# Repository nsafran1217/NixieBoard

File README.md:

This repo contains an Arduino Library and board disign files for a 6 digit IN-12 Nixie tube board with INS-1 colons.

The board uses K155ID1 drivers to control the tubes.

This is a smaller version of my original Nixie tube clock board: https://github.com/nsafran1217/arduino-nixie-clock

Used in my Nixie Weather Clock project: https://github.com/nsafran1217/NixieWeatherClock

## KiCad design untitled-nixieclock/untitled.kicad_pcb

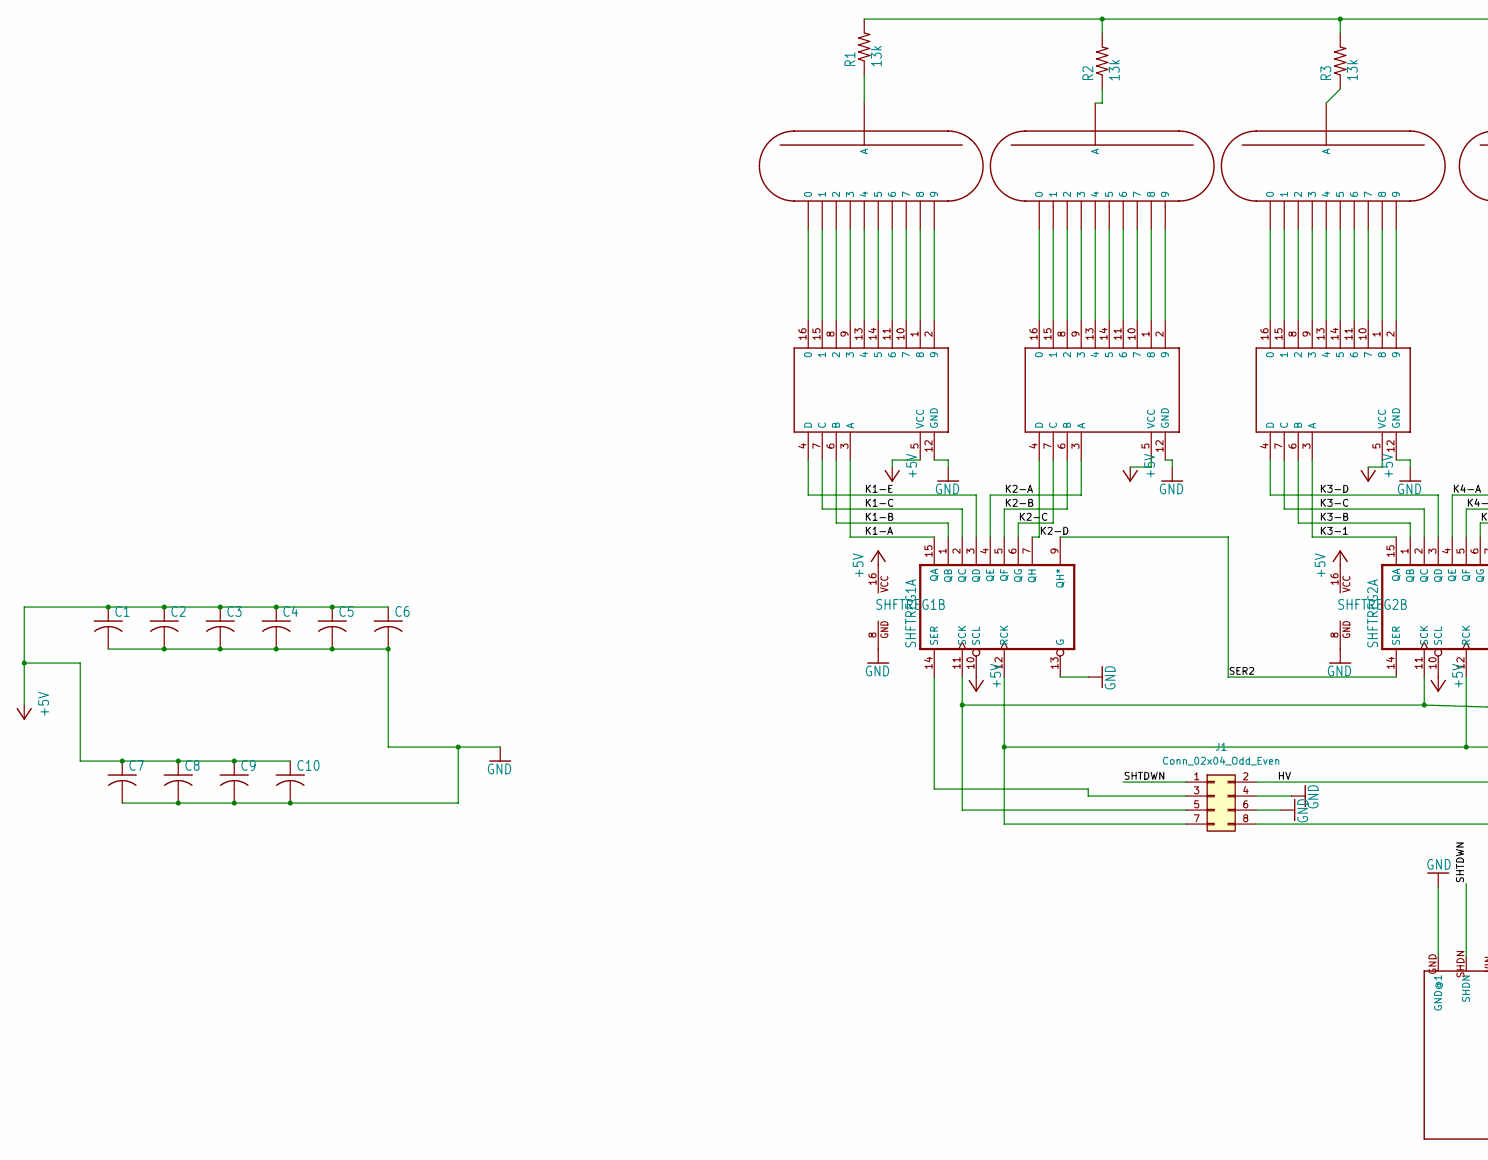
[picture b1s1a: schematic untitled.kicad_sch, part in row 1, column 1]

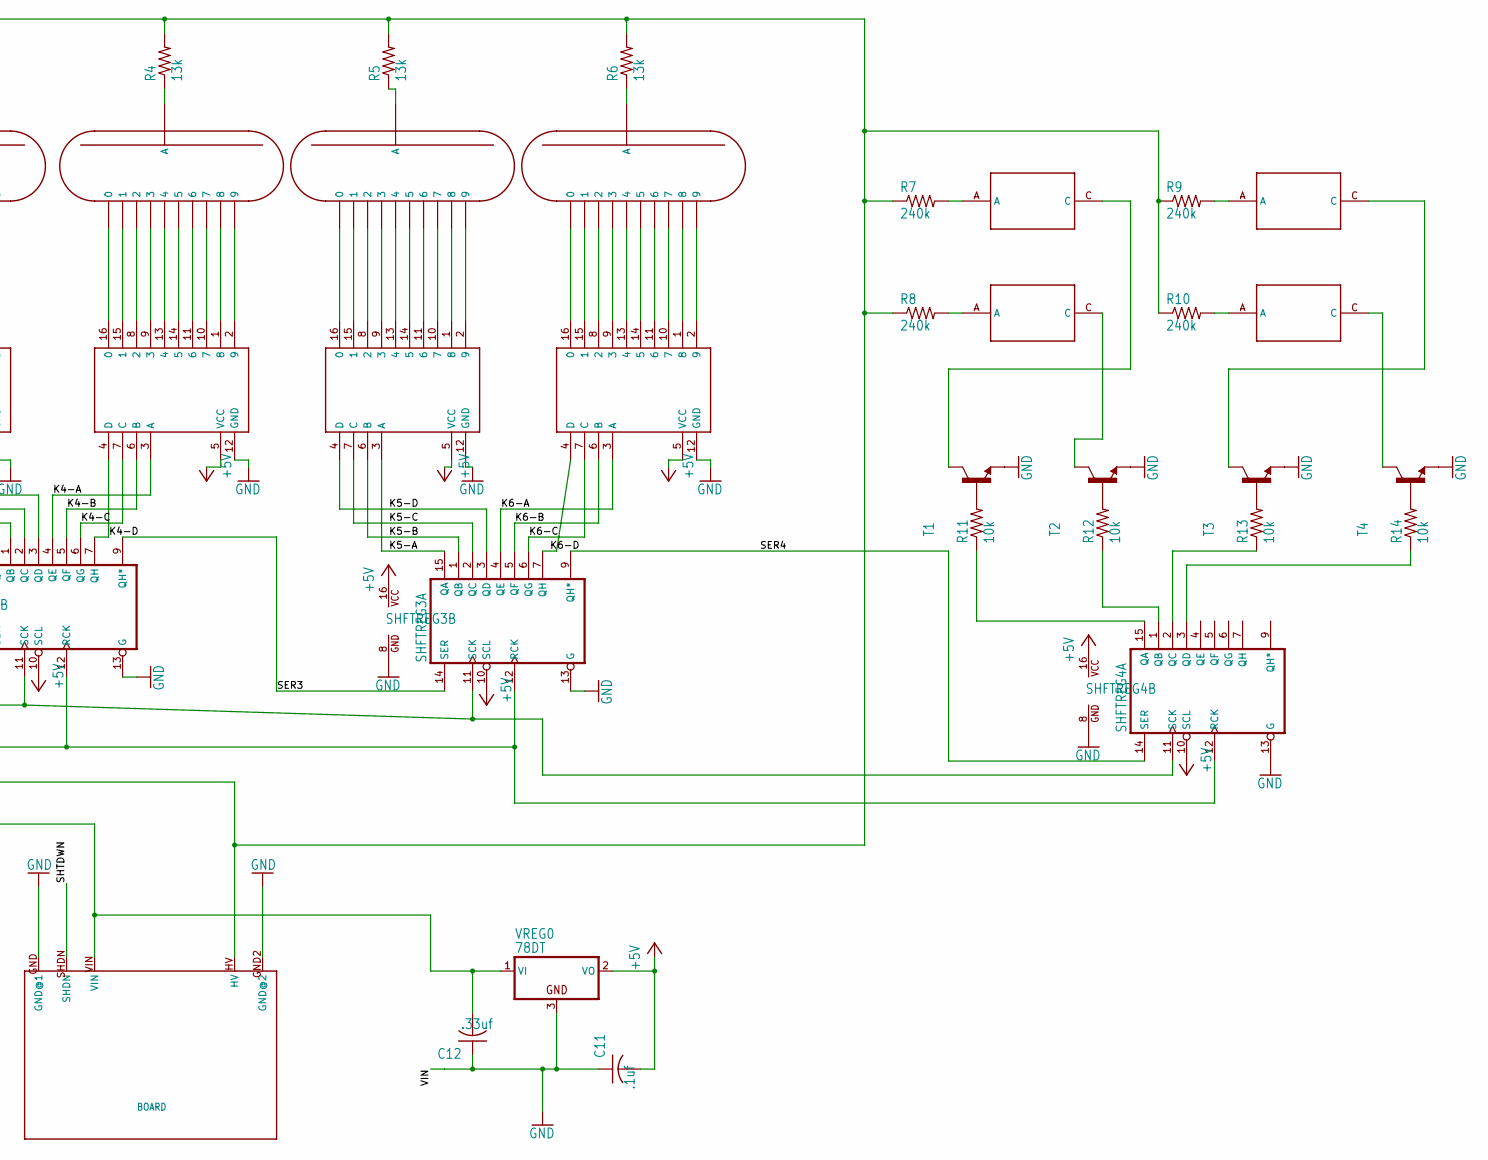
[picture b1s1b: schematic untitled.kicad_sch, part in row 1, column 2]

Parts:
C1, C2, C3, C4, C5, C6, C7, C8, C9, C10: C-USC0805; C_0805_2012Metric_Pad1.18x1.45mm_HandSolder
C11: .1uf; C_0805_2012Metric_Pad1.18x1.45mm_HandSolder
C12: .33uf; C_0805_2012Metric_Pad1.18x1.45mm_HandSolder
DRV1, DRV2, DRV3, DRV4, DRV5, DRV6: К155ИД1; DIP-16_W7.62mm
HV_POWER0: BOARD
IN1, IN2, IN3, IN4: INS-1
J1: Conn_02x04_Odd_Even; IDC-Header_2x04_P2.54mm_Vertical
N1, N2, N3, N4, N5, N6: IN-12A; IN-12
R1, R2, R3, R4, R5, R6: 13k; R_0805_2012Metric_Pad1.20x1.40mm_HandSolder
R7, R8, R9, R10: 240k; R_0805_2012Metric_Pad1.20x1.40mm_HandSolder
R11, R12, R13, R14: 10k; R_0805_2012Metric_Pad1.20x1.40mm_HandSolder
SHFTREG1, SHFTREG2, SHFTREG3, SHFTREG4: 74595N; DIP-16_W7.62mm
T1, T2, T3, T4: -NPN-SOT23-BEC; SOT-23_Handsoldering
VREG0: 78DT; TO252

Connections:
+5V: C1.1, C2.1, C3.1, C4.1, C5.1, C6.1, C7.1, C8.1, C9.1, C10.1, C11.2, DRV1.5 (VCC), DRV2.5 (VCC), DRV3.5 (VCC), DRV4.5 (VCC), DRV5.5 (VCC), DRV6.5 (VCC), SHFTREG1.10 (SCL), SHFTREG1.16 (VCC), SHFTREG2.10 (SCL), SHFTREG2.16 (VCC), SHFTREG3.10 (SCL), SHFTREG3.16 (VCC), SHFTREG4.10 (SCL), SHFTREG4.16 (VCC), VREG0.2 (VO)
/HV: HV_POWER0.HV, J1.2, R1.2, R2.2, R3.2, R4.2, R5.2, R6.2, R7.1, R8.1, R9.1, R10.1
/K1-A: DRV1.3 (A), SHFTREG1.15 (QA)
/K1-B: DRV1.6 (B), SHFTREG1.1 (QB)
/K1-C: DRV1.7 (C), SHFTREG1.2 (QC)
/K1-E: DRV1.4 (D), SHFTREG1.3 (QD)
/K2-A: DRV2.3 (A), SHFTREG1.4 (QE)
/K2-B: DRV2.6 (B), SHFTREG1.5 (QF)
/K2-C: DRV2.7 (C), SHFTREG1.6 (QG)
/K2-D: DRV2.4 (D), SHFTREG1.7 (QH)
/K3-1: DRV3.3 (A), SHFTREG2.15 (QA)
/K3-B: DRV3.6 (B), SHFTREG2.1 (QB)
/K3-C: DRV3.7 (C), SHFTREG2.2 (QC)
/K3-D: DRV3.4 (D), SHFTREG2.3 (QD)
/K4-A: DRV4.3 (A), SHFTREG2.4 (QE)
/K4-B: DRV4.6 (B), SHFTREG2.5 (QF)
/K4-C: DRV4.7 (C), SHFTREG2.6 (QG)
/K4-D: DRV4.4 (D), SHFTREG2.7 (QH)
/K5-A: DRV5.3 (A), SHFTREG3.15 (QA)
/K5-B: DRV5.6 (B), SHFTREG3.1 (QB)
/K5-C: DRV5.7 (C), SHFTREG3.2 (QC)
/K5-D: DRV5.4 (D), SHFTREG3.3 (QD)
/K6-A: DRV6.3 (A), SHFTREG3.4 (QE)
/K6-B: DRV6.6 (B), SHFTREG3.5 (QF)
/K6-C: DRV6.7 (C), SHFTREG3.6 (QG)
/K6-D: DRV6.4 (D), SHFTREG3.7 (QH)
/SER2: SHFTREG1.9 (QH*), SHFTREG2.14 (SER)
/SER3: SHFTREG2.9 (QH*), SHFTREG3.14 (SER)
/SER4: SHFTREG3.9 (QH*), SHFTREG4.14 (SER)
/SHTDWN: HV_POWER0.SHDN, J1.1
GND: C1.2, C2.2, C3.2, C4.2, C5.2, C6.2, C7.2, C8.2, C9.2, C10.2, C11.1, C12.1, DRV1.12 (GND), DRV2.12 (GND), DRV3.12 (GND), DRV4.12 (GND), DRV5.12 (GND), DRV6.12 (GND), HV_POWER0.GND (GND@1), HV_POWER0.GND2 (GND@2), J1.4, J1.6, SHFTREG1.8 (GND), SHFTREG1.13 (G), SHFTREG2.8 (GND), SHFTREG2.13 (G), SHFTREG3.8 (GND), SHFTREG3.13 (G), SHFTREG4.8 (GND), SHFTREG4.13 (G), T1.2 (E), T2.2 (E), T3.2 (E), T4.2 (E), VREG0.3 (GND)
unnamed: DRV1.16 (0), N1.0
unnamed: DRV1.15 (1), N1.1
unnamed: DRV1.8 (2), N1.2
unnamed: DRV1.9 (3), N1.3
unnamed: DRV1.13 (4), N1.4
unnamed: DRV1.14 (5), N1.5
unnamed: DRV1.11 (6), N1.6
unnamed: DRV1.10 (7), N1.7
unnamed: DRV1.1 (8), N1.8
unnamed: DRV1.2 (9), N1.9
unnamed: DRV2.16 (0), N2.0
unnamed: DRV2.15 (1), N2.1
unnamed: DRV2.8 (2), N2.2
unnamed: DRV2.9 (3), N2.3
unnamed: DRV2.13 (4), N2.4
unnamed: DRV2.14 (5), N2.5
unnamed: DRV2.11 (6), N2.6
unnamed: DRV2.10 (7), N2.7
unnamed: DRV2.1 (8), N2.8
unnamed: DRV2.2 (9), N2.9
unnamed: DRV3.16 (0), N3.0
unnamed: DRV3.15 (1), N3.1
unnamed: DRV3.8 (2), N3.2
unnamed: DRV3.9 (3), N3.3
unnamed: DRV3.13 (4), N3.4
unnamed: DRV3.14 (5), N3.5
unnamed: DRV3.11 (6), N3.6
unnamed: DRV3.10 (7), N3.7
unnamed: DRV3.1 (8), N3.8
unnamed: DRV3.2 (9), N3.9
unnamed: DRV4.16 (0), N4.0
unnamed: DRV4.15 (1), N4.1
unnamed: DRV4.8 (2), N4.2
unnamed: DRV4.9 (3), N4.3
unnamed: DRV4.13 (4), N4.4
unnamed: DRV4.14 (5), N4.5
unnamed: DRV4.11 (6), N4.6
unnamed: DRV4.10 (7), N4.7
unnamed: DRV4.1 (8), N4.8
unnamed: DRV4.2 (9), N4.9
unnamed: DRV5.16 (0), N5.0
unnamed: DRV5.15 (1), N5.1
unnamed: DRV5.8 (2), N5.2
unnamed: DRV5.9 (3), N5.3
unnamed: DRV5.13 (4), N5.4
unnamed: DRV5.14 (5), N5.5
unnamed: DRV5.11 (6), N5.6
unnamed: DRV5.10 (7), N5.7
unnamed: DRV5.1 (8), N5.8
unnamed: DRV5.2 (9), N5.9
unnamed: DRV6.16 (0), N6.0
unnamed: DRV6.15 (1), N6.1
unnamed: DRV6.8 (2), N6.2
unnamed: DRV6.9 (3), N6.3
unnamed: DRV6.13 (4), N6.4
unnamed: DRV6.14 (5), N6.5
unnamed: DRV6.11 (6), N6.6
unnamed: DRV6.10 (7), N6.7
unnamed: DRV6.1 (8), N6.8
unnamed: DRV6.2 (9), N6.9
unnamed: IN1.A, R7.2
unnamed: IN2.A, R8.2
unnamed: IN3.A, R9.2
unnamed: IN4.A, R10.2
unnamed: J1.3, SHFTREG1.14 (SER)
unnamed: J1.5, SHFTREG1.11 (SCK), SHFTREG2.11 (SCK), SHFTREG3.11 (SCK), SHFTREG4.11 (SCK)
unnamed: J1.7, SHFTREG1.12 (RCK), SHFTREG2.12 (RCK), SHFTREG3.12 (RCK), SHFTREG4.12 (RCK)
unnamed: C12.2, HV_POWER0.VIN, J1.8, VREG0.1 (VI)
unnamed: N1.A, R1.1
unnamed: N2.A, R2.1
unnamed: N3.A, R3.1
unnamed: N4.A, R4.1
unnamed: N5.A, R5.1
unnamed: N6.A, R6.1
unnamed: R11.1, SHFTREG4.15 (QA)
unnamed: R12.1, SHFTREG4.1 (QB)
unnamed: R13.1, SHFTREG4.2 (QC)
unnamed: R14.1, SHFTREG4.3 (QD)
unnamed: R11.2, T1.1 (B)
unnamed: IN1.C, T1.3 (C)
unnamed: R12.2, T2.1 (B)
unnamed: IN2.C, T2.3 (C)
unnamed: R13.2, T3.1 (B)
unnamed: IN3.C, T3.3 (C)
unnamed: R14.2, T4.1 (B)
unnamed: IN4.C, T4.3 (C)

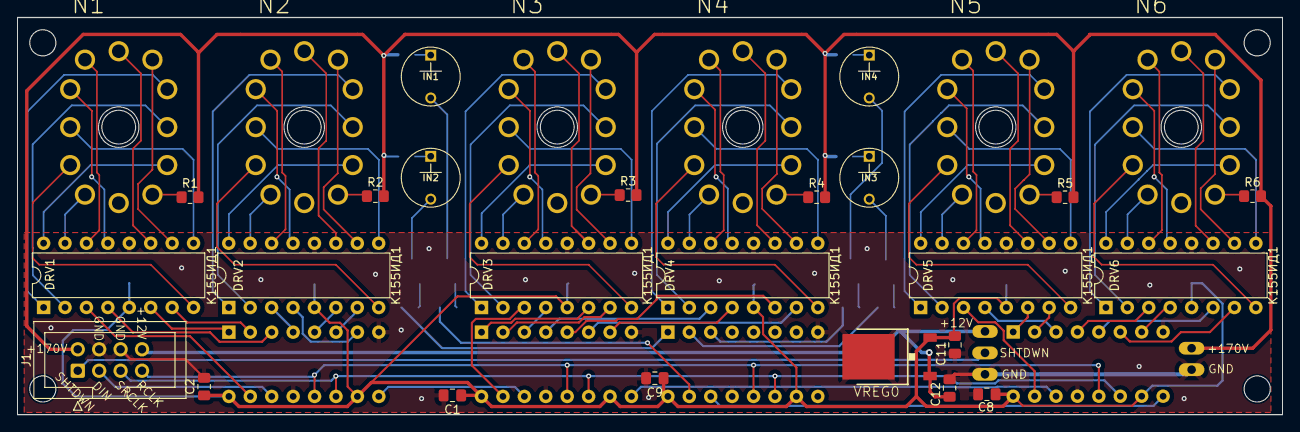
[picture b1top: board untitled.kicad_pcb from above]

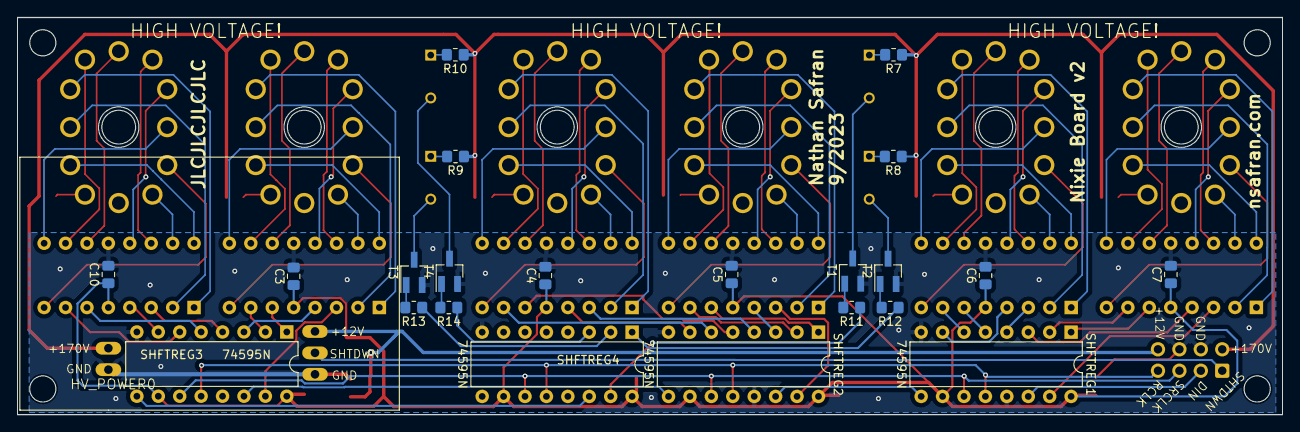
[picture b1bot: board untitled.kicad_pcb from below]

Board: 2 copper layers, 150.0 x 47.1 mm, 63 parts (23 on the bottom side), 117 nets.

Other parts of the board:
@HOLE0, @HOLE1, @HOLE2, @HOLE3, @HOLE4, @HOLE5, @HOLE6, @HOLE7, @HOLE8, @HOLE9: (no value)

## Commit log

2023-09-08 Init commit
2023-09-08 Add divider defines; add some comments
2023-09-11 Change var types, simplify some code
2023-10-04 Add board files
